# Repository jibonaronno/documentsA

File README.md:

# PDA IEC-61850 References

1. __LU_102_A__ Backup
2. __LU_104_A__ Backup
3. __ClientProc__ executable with SA_Client.ini and YH.cid files Backup
4. __SclManager__ Backup
___
SA_Client.ini has following configs:
```ini
LocalIp=192.168.10.105
...
...
PATH=D:/develop/MZAutomation/SAProgram/ClientProc_2017_Dev_NoTimer_Minsu/ClientProc/61850_CFG/CFG/61850/SA_CFG
SAVE_PATH =D:/develop/MZAutomation/SAProgram/ClientProc_2017_Dev_NoTimer_Minsu/ClientProc/61850_CFG/LOG/61850
ENG_PATH =D:/develop/MZAutomation/SAProgram/ClientProc_2017_Dev_NoTimer_Minsu/ClientProc/61850_CFG/DB/ied_info_gw.csv
```
These configurations should be changed if machine or location is changed. 

It is required to change settings using __SCLManager.exe__ when required for new setup.

<br>

Confluence Pages From PDA
ACQ Operation and calculation / Integration of various current values
Copy of 차단기 동작 특성 페이지
https://jlee193.atlassian.net/wiki/spaces/PDA/pages/514129921/Copy+of

Bushing Documentation Page From PDA 
부싱 누설 전류 페이지
https://jlee193.atlassian.net/wiki/spaces/PDA/pages/296812597

An Initial Concept of hardware pptx file downloaded in Confluence folder
종합예방진단시스템(20210625)_HW팀.pptx
하드웨어 구성
https://jlee193.atlassian.net/wiki/spaces/PDA/pages/154042616

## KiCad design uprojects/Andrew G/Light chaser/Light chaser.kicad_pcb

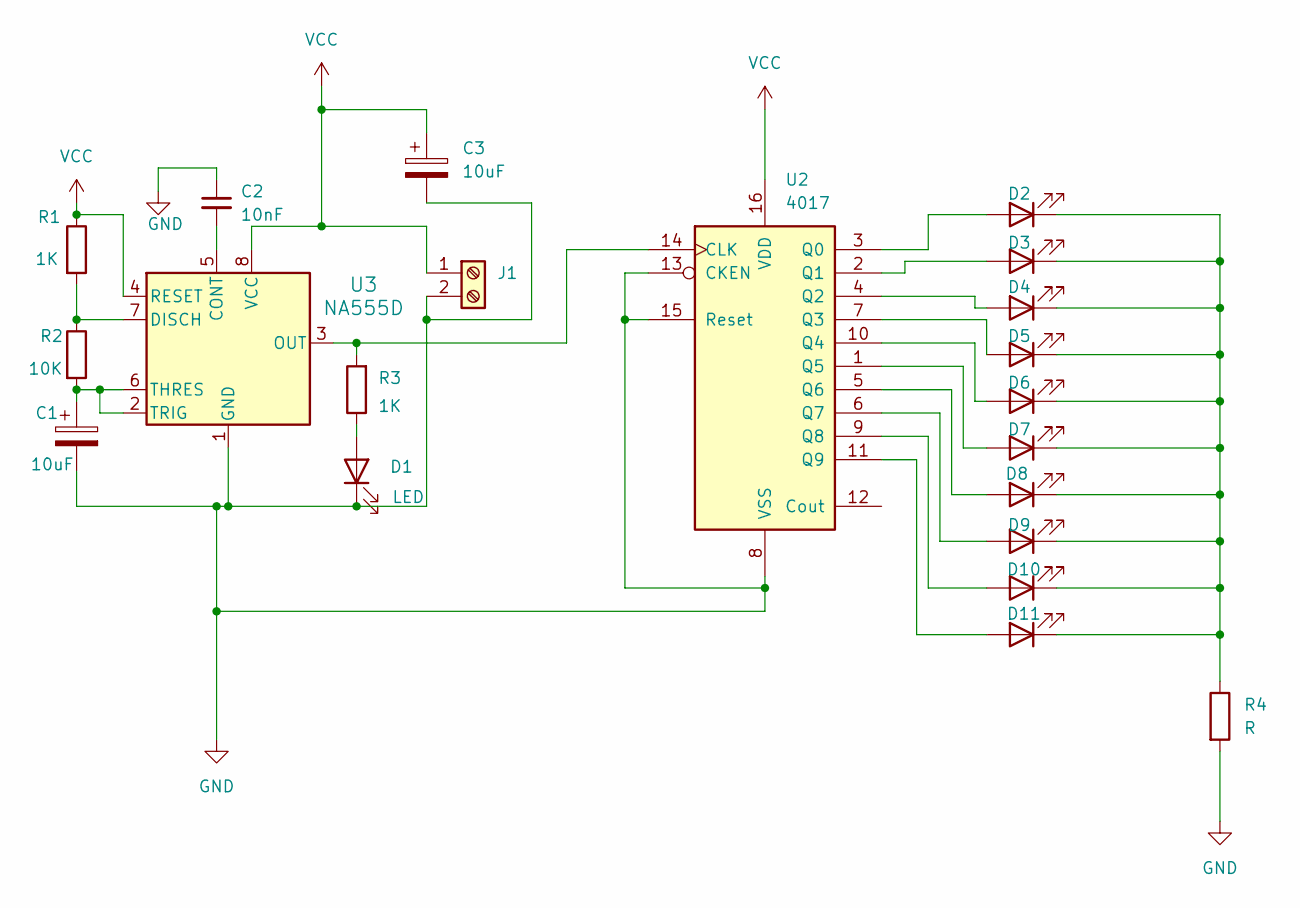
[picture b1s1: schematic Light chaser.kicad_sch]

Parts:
C1: 10uF; CP_Radial_D5.0mm_P2.00mm
C2: 10nF; C_Disc_D3.0mm_W1.6mm_P2.50mm
C3: 10uF; CP_Radial_D10.0mm_P5.00mm
D1, D2, D3, D4, D5, D6, D7, D8, D9, D10, D11: LED; LED_D5.0mm
J1: Screw_Terminal_01x02; TerminalBlock_MaiXu_MX126-5.0-02P_1x02_P5.00mm
R1, R3: 1K; R_Axial_DIN0204_L3.6mm_D1.6mm_P7.62mm_Horizontal
R2: 10K; R_Axial_DIN0204_L3.6mm_D1.6mm_P7.62mm_Horizontal
R4: R; R_Axial_DIN0204_L3.6mm_D1.6mm_P7.62mm_Horizontal
U2: 4017; SO-16_3.9x9.9mm_P1.27mm
U3: NA555D; D8

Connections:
GND: C1.2, C2.1, C3.2, D1.1 (K), J1.2, R4.2, U2.8 (VSS), U2.13 (CKEN), U2.15 (Reset), U3.1 (GND)
unnamed: D1.2 (A), R3.1
unnamed: D2.2 (A), U2.3 (Q0)
unnamed: D3.2 (A), U2.2 (Q1)
unnamed: D4.2 (A), U2.4 (Q2)
unnamed: D5.2 (A), U2.7 (Q3)
unnamed: D6.2 (A), U2.10 (Q4)
unnamed: D7.2 (A), U2.1 (Q5)
unnamed: D8.2 (A), U2.5 (Q6)
unnamed: D9.2 (A), U2.6 (Q7)
unnamed: D10.2 (A), U2.9 (Q8)
unnamed: D2.1 (K), D3.1 (K), D4.1 (K), D5.1 (K), D6.1 (K), D7.1 (K), D8.1 (K), D9.1 (K), D10.1 (K), D11.1 (K), R4.1
unnamed: D11.2 (A), U2.11 (Q9)
unnamed: R3.2, U2.14 (CLK), U3.3 (OUT)
unnamed: C2.2, U3.5 (CONT)
unnamed: R1.2, R2.1, U3.7 (DISCH)
unnamed: C1.1, R2.2, U3.2 (TRIG), U3.6 (THRES)
VCC: C3.1, J1.1, R1.1, U2.16 (VDD), U3.4 (RESET), U3.8 (VCC)

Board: 2 copper layers, 21 parts (0 on the bottom side), 18 nets, no tracks yet.

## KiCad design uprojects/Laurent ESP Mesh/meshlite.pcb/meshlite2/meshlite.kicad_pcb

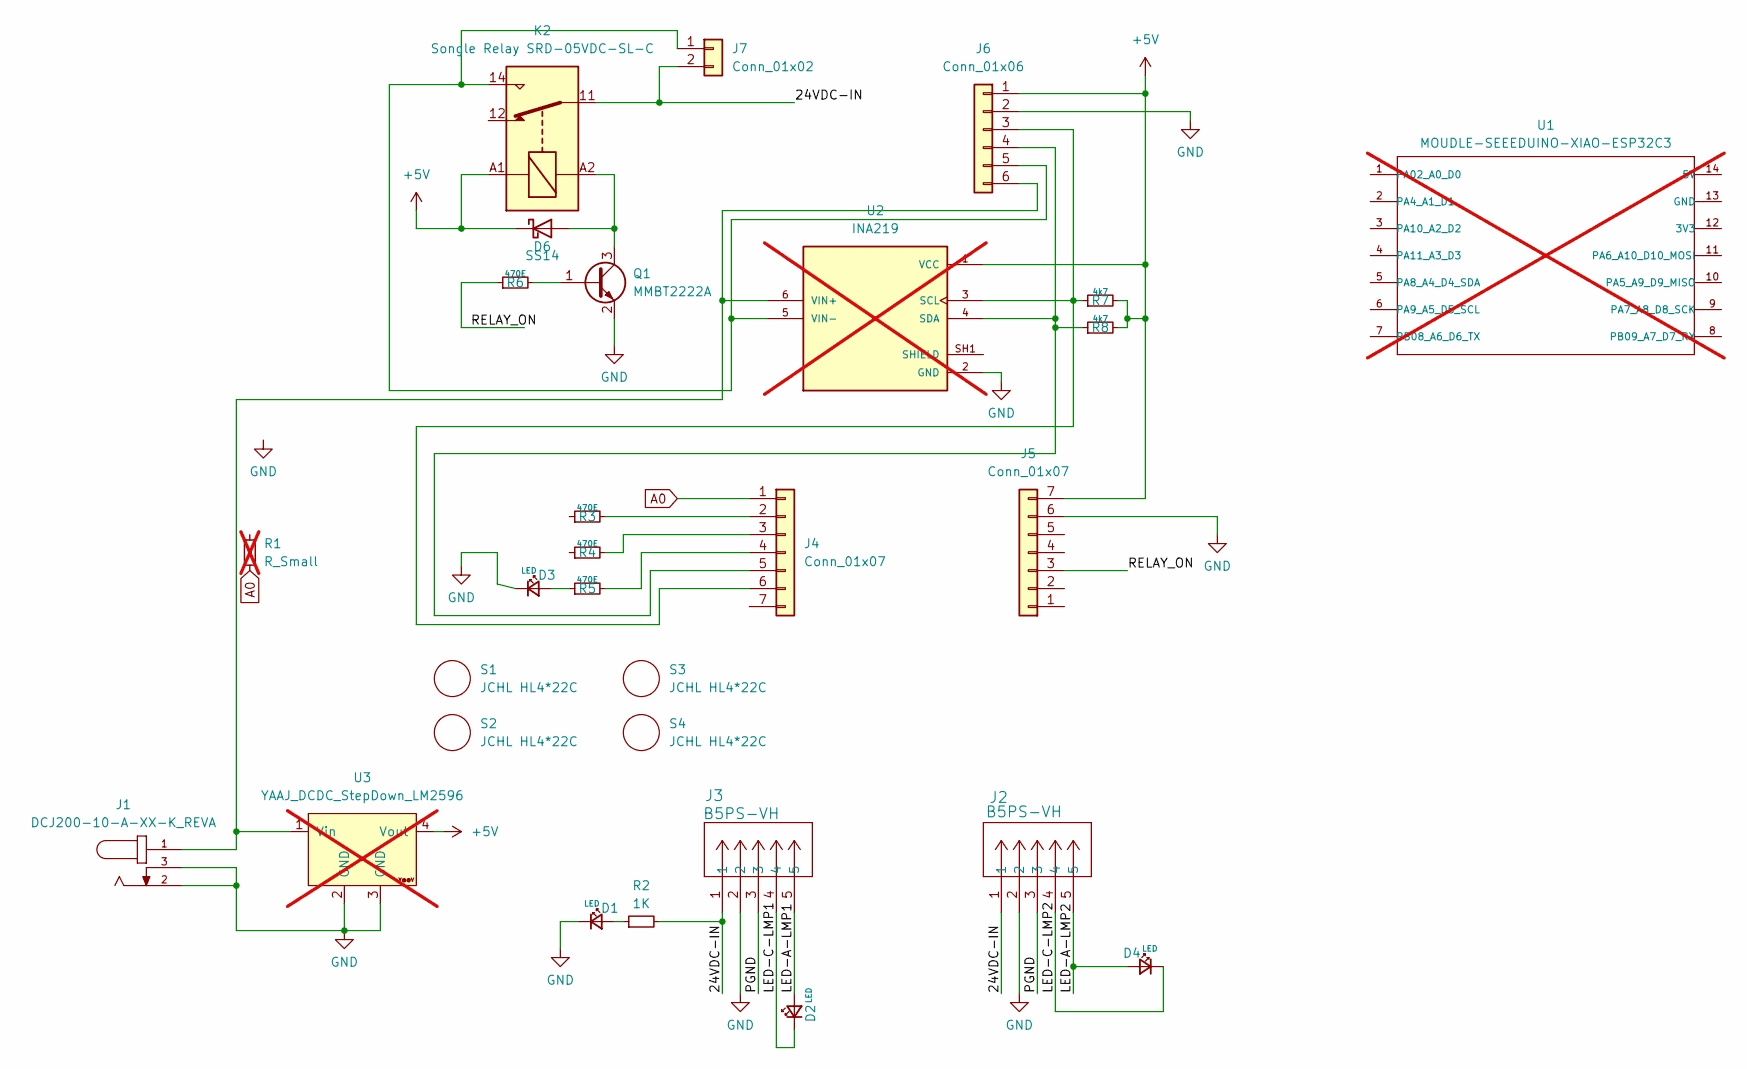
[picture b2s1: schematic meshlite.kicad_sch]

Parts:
D1, D2, D3, D4: LED; LED_D3.0mm; LCSC C473831
D6: SS14; D_SMA; LCSC C83852
J1: DCJ200-10-A-XX-K_REVA; GCT_DCJ200-10-A-XX-K_REVA; PARTREV A; LCSC C720557
J2, J3: B5PS-VH; CONN_B5PS-VH_JST; LCSC C157989
J4, J5: Conn_01x07; PinSocket_1x07_P2.54mm_Vertical; LCSC C492406
J6: Conn_01x06; PinSocket_1x06_P2.54mm_Vertical; LCSC C42431807
J7: Conn_01x02; PinHeader_1x02_P2.54mm_Vertical; LCSC C492401
K2: Songle Relay SRD-05VDC-SL-C; Relay_SPDT_Finder_36.11; LCSC C35449
Q1: MMBT2222A; SOT-23; LCSC C82460
R1: R_Small; R_0603_1608Metric; not fitted
R2: 1K; R_0603_1608Metric; LCSC C22548
R3, R4, R5, R6: 470E; R_0603_1608Metric; LCSC C114669
R7, R8: 4k7; R_0603_1608Metric; LCSC C99782
S1, S2, S3, S4: JCHL HL4*22C; SPACER_01; LCSC C48735534
U1: MOUDLE-SEEEDUINO-XIAO-ESP32C3; MOUDLE14P-SMD-2.54-21X17.8MM; not fitted
U2: INA219; MODULE_INA219; PARTREV C; not fitted
U3: YAAJ_DCDC_StepDown_LM2596; not fitted

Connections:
+5V: D6.1 (K), J5.7, J6.1, K2.A1, R7.2, R8.2, U2.1 (VCC), U3.4 (Vout)
/24VDC-IN: J2.1, J3.1, J7.2, K2.11, R2.2
/LED-A-LMP1: D2.2 (A), J3.5
/LED-A-LMP2: D4.2 (A), J2.5
/LED-C-LMP1: D2.1 (K), J3.4
/LED-C-LMP2: D4.1 (K), J2.4
/PGND: J2.3, J3.3
/RELAY_ON: J4.7, J5.3, R6.1
A0: J4.1, R1.2
GND: D1.1 (K), D3.1 (K), J1.2, J1.3, J2.2, J3.2, J5.6, J6.2, Q1.2 (E), U2.2 (GND), U3.2 (GND), U3.3 (GND)
unnamed: D1.2 (A), R2.1
unnamed: D3.2 (A), R5.1
unnamed: D6.2 (A), K2.A2, Q1.3 (C)
unnamed: J4.2, R3.2
unnamed: J4.3, R4.2
unnamed: J4.4, R5.2
unnamed: J4.5, J6.4, R8.1, U2.4 (SDA)
unnamed: J4.6, J6.3, R7.1, U2.3 (SCL)
unnamed: J6.5, J7.1, K2.14, U2.5 (VIN-), U2.VIN-
unnamed: J1.1, J6.6, U2.6 (VIN+), U2.VIN+, U3.1 (Vin)
unnamed: Q1.1 (B), R6.2
unnamed: U2.SH1 (SHIELD), U2.SH2 (SHIELD), U2.SH3 (SHIELD), U2.SH4 (SHIELD)

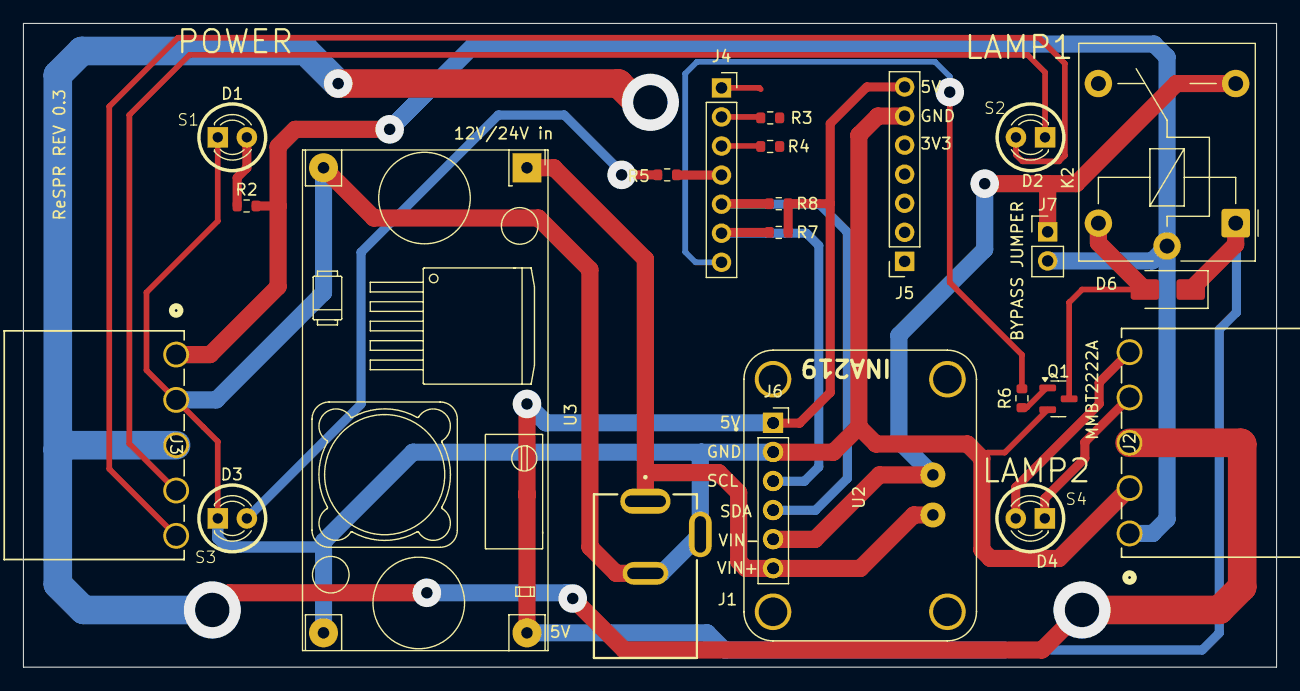
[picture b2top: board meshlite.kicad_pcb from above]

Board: 2 copper layers, 109.5 x 56.2 mm, 27 parts (0 on the bottom side), 21 nets.

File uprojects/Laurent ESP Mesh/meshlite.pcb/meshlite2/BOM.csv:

"Reference","Qty","Value","LCSC"
"D1,D2,D3,D4","4","LED","C473831"
"D6","1","SS14","C83852"
"J1","1","DCJ200-10-A-XX-K_REVA","C720557"
"J2,J3","2","B5PS-VH","C157989"
"J4,J5","2","Conn_01x07","C492406"
"J6","1","Conn_01x06","C42431807"
"J7","1","Conn_01x02","C492401"
"K2","1","Songle Relay SRD-05VDC-SL-C","C35449"
"Q1","1","MMBT2222A","C82460"
"R2","1","1K","C22548"
"R3,R4,R5,R6","4","470E","C114669"
"R7,R8","2","4k7","C99782"
"S1,S2,S3,S4","4","JCHL HL4*22C","C48735534"

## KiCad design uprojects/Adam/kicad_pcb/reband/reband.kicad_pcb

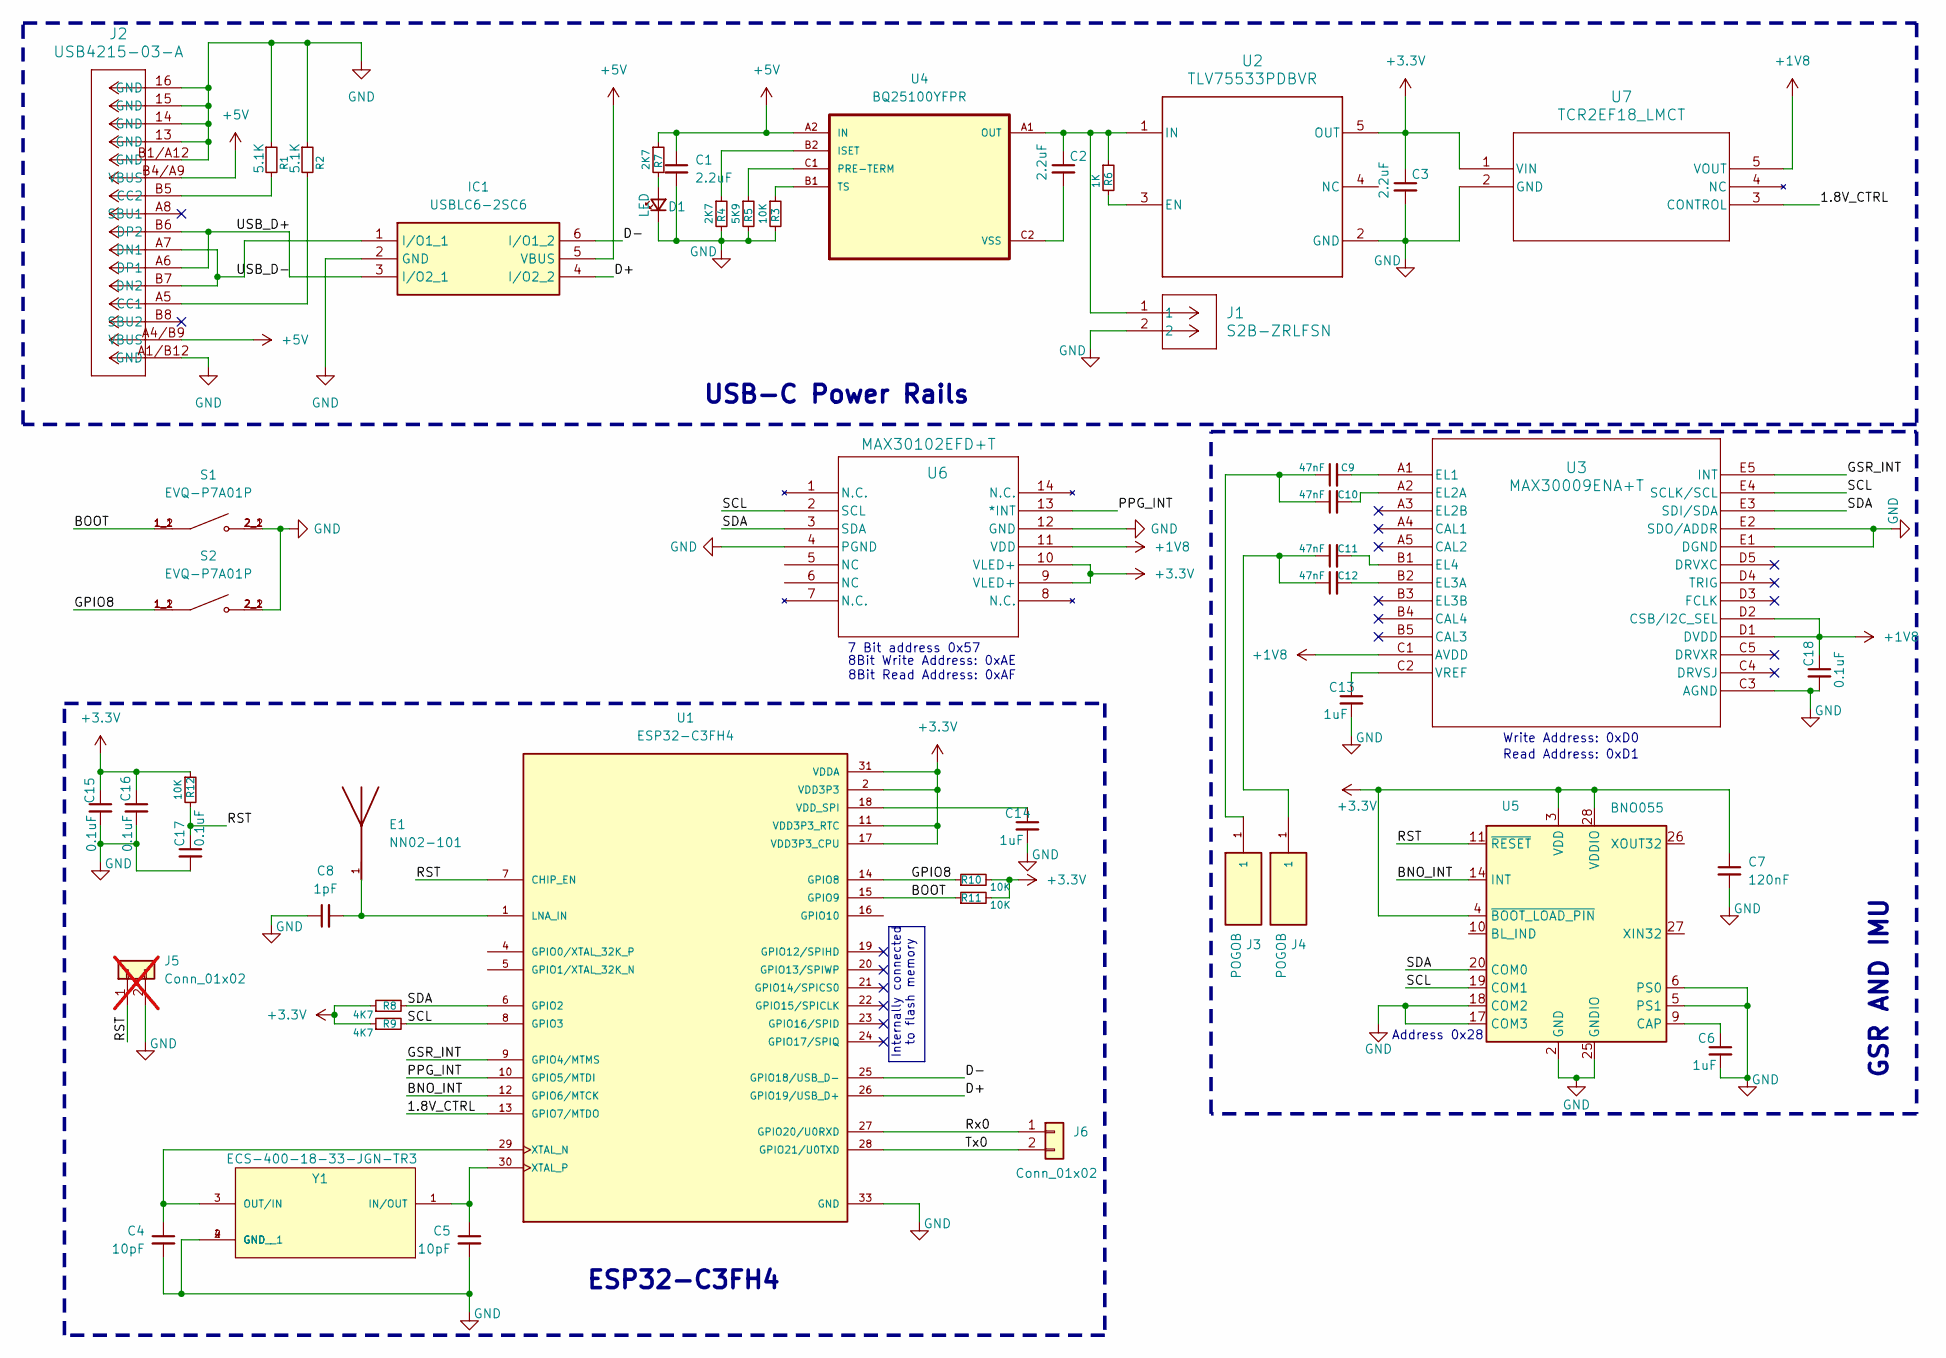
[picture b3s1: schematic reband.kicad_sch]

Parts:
C1, C2, C3: 2.2uF; C_0402_1005Metric_Pad0.74x0.62mm_HandSolder; Manufacturer_Part_Number TMK105CBJ225MV-F; DigiKey 587-6022-2-ND
C4, C5: 10pF; C_0402_1005Metric_Pad0.74x0.62mm_HandSolder; Manufacturer_Part_Number GRM1555C1H100FA01D; DigiKey 490-6186-2-ND
C6, C13, C14: 1uF; C_0402_1005Metric_Pad0.74x0.62mm_HandSolder; Manufacturer_Part_Number JMK105BJ105KV-F; DigiKey 587-1231-2-ND
C7: 120nF; C_0402_1005Metric_Pad0.74x0.62mm_HandSolder; Manufacturer_Part_Number CC0402KRX5R6BB124; DigiKey 13-CC0402KRX5R6BB124TR-ND
C8: 1pF; C_0402_1005Metric_Pad0.74x0.62mm_HandSolder; Manufacturer_Part_Number GJM1555C1H1R0BB01D; DigiKey 490-6073-2-ND
C9, C10, C11, C12: 47nF; C_0402_1005Metric_Pad0.74x0.62mm_HandSolder; Manufacturer_Part_Number GRM155R71H472KA01D; DigiKey 490-1308-2-ND
C15, C16, C17, C18: 0.1uF; C_0402_1005Metric_Pad0.74x0.62mm_HandSolder; Manufacturer_Part_Number CL05B104KP5NNNC; DigiKey 1276-1002-2-ND
D1: LED; LED_0402_1005Metric_Pad0.77x0.64mm_HandSolder; Manufacturer_Part_Number XZMDK68W-2; DigiKey 1497-1174-2-ND
E1: NN02-101; XCVR_NN02-101; PARTREV May 2021; DigiKey 2115-NN02-101TR-ND
IC1: USBLC6-2SC6; SOT95P280X145-6N; Manufacturer_Part_Number USBLC6-2SC6; Mouser Part Number 511-USBLC6-2SC6
J1: S2B-ZRLFSN; CONN_S2B-ZR_JST; Manufacturer_Part_Number S2B-ZR; DigiKey 455-1669-ND
J2: USB4215-03-A; CONN_8p94X6p5X3p16_12L_GCC; Manufacturer_Part_Number USB4215-03-A; DigiKey 2073-USB4215-03-ATR-ND
J3, J4: POGOB; PARTREV N/A; DigiKey ED90453TR-ND
J5: Conn_01x02; PinHeader_1x02_P1.00mm_Vertical; Manufacturer_Part_Number BC020-02-A-0200-0300-L-G; DigiKey 2073-BC020-02-A-0200-0300-L-G-ND; not fitted
J6: Conn_01x02; PinHeader_1x02_P1.00mm_Vertical_SMD_Pin1Left
R1, R2: 5.1K; R_0402_1005Metric_Pad0.72x0.64mm_HandSolder; Manufacturer_Part_Number RC0402FR-075K1L; DigiKey 311-5.10KLRTR-ND
R3, R10, R11, R12: 10K; R_0402_1005Metric_Pad0.72x0.64mm_HandSolder; Manufacturer_Part_Number RMCF0402FT10K0; DigiKey RMCF0402FT10K0TR-ND
R4, R7: 2K7; R_0402_1005Metric_Pad0.72x0.64mm_HandSolder; Manufacturer_Part_Number CRGCQ0402F2K7; DigiKey A129632TR-ND
R5: 5K9; R_0402_1005Metric_Pad0.72x0.64mm_HandSolder; Manufacturer_Part_Number ERJ-2RKF5901X; DigiKey P5.90KLTR-ND
R6: 1K; R_0402_1005Metric_Pad0.72x0.64mm_HandSolder; Manufacturer_Part_Number RC0402FR-071KL; DigiKey 311-1.00KLRTR-ND
R8, R9: 4K7; R_0402_1005Metric_Pad0.72x0.64mm_HandSolder; Manufacturer_Part_Number RC0402JR-074K7L; DigiKey 311-4.7KJRTR-ND
S1, S2: EVQ-P7A01P; SW_EVQ-P7A01P; PARTREV 2022.4; DigiKey P16763TR-ND
U1: ESP32-C3FH4; QFN50P500X500X90-33N; PARTREV 2.0; DigiKey 1904-ESP32-C3FH4TR-ND
U2: TLV75533PDBVR; DBV0005A_N; Manufacturer_Part_Number TLV75533PDBVR; DigiKey 296-50411-2-ND
U3: MAX30009ENA+T; MAX30009ENA_T; Manufacturer_Part_Number MAX30009ENA+T; DigiKey 175-MAX30009ENA+TTR-ND
U4: BQ25100YFPR; BGA6N40P3X2_157X88X50N; Manufacturer_Part_Number BQ25100YFPR; DigiKey 296-39931-2-ND
U5: BNO055; LGA-28_5.2x3.8mm_P0.5mm; Manufacturer_Part_Number BNO055; DigiKey 828-1058-2-ND
U6: MAX30102EFD+T; 21-1048_F143A5&plus_1_MXM; Manufacturer_Part_Number MAX30102EFD+T; DigiKey MAX30102EFD+TTR-ND
U7: TCR2EF18_LMCT; SOT-25 SMV_TOS; Manufacturer_Part_Number TCR2EF18,LM(CT; DigiKey TCR2EF18LM(CTTR-ND
Y1: ECS-400-18-33-JGN-TR3; XTAL_ECS-400-18-33-JGN-TR3; Manufacturer_Part_Number ECS-400-18-33-JGN-TR3; DigiKey 50-ECS-400-18-33-JGN-TR3TR-ND

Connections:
+1V8: C18.1, U3.C1 (AVDD), U3.D1 (DVDD), U3.D2 (CSB/I2C_SEL), U6.11 (VDD), U7.5 (VOUT)
+3.3V: C3.1, C7.1, C15.1, C16.1, R8.1, R9.1, R10.2, R11.2, R12.1, U1.2 (VDD3P3), U1.3 (VDD3P3), U1.11 (VDD3P3_RTC), U1.17 (VDD3P3_CPU), U1.31 (VDDA), U1.32 (VDDA), U2.5 (OUT), U5.3 (VDD), U5.4 (~BOOT_LOAD_PIN), U5.28 (VDDIO), U6.9 (VLED+), U6.10 (VLED+), U7.1 (VIN)
+5V: C1.1, IC1.5 (VBUS), J2.A4/B9 (VBUS), J2.B4/A9 (VBUS), R7.1, U4.A2 (IN)
/1.8V_CTRL: U1.13 (GPIO7/MTDO), U7.3 (CONTROL)
/BNO_INT: U1.12 (GPIO6/MTCK), U5.14 (INT)
/BOOT: R11.1, S1.1_1, S1.1_2, U1.15 (GPIO9)
/D+: IC1.4 (I/O2_2), U1.26 (GPIO19/USB_D+)
/D-: IC1.6 (I/O1_2), U1.25 (GPIO18/USB_D-)
/GPIO8: R10.1, S2.1_1, S2.1_2, U1.14 (GPIO8)
/GSR_INT: U1.9 (GPIO4/MTMS), U3.E5 (INT)
/PPG_INT: U1.10 (GPIO5/MTDI), U6.13 (*INT)
/RST: C17.1, J5.1, R12.2, U1.7 (CHIP_EN), U5.11 (~RESET)
/Rx0: J6.1, U1.27 (GPIO20/U0RXD)
/SCL: R9.2, U1.8 (GPIO3), U3.E4 (SCLK/SCL), U5.19 (COM1), U6.2 (SCL)
/SDA: R8.2, U1.6 (GPIO2), U3.E3 (SDI/SDA), U5.20 (COM0), U6.3 (SDA)
/Tx0: J6.2, U1.28 (GPIO21/U0TXD)
/USB_D+: IC1.3 (I/O2_1), J2.A6 (DP1), J2.B6 (DP2)
/USB_D-: IC1.1 (I/O1_1), J2.A7 (DN1), J2.B7 (DN2)
unnamed: C9.1, C10.1, J3.1 (1_1)
unnamed: C11.1, C12.1, J4.1 (1_1)
unnamed: D1.2 (A), R7.2
unnamed: J2.A5 (CC1), R2.2
unnamed: J2.B5 (CC2), R1.2
unnamed: C14.1, U1.18 (VDD_SPI)
unnamed: C4.1, U1.29 (XTAL_N), Y1.3 (OUT/IN)
unnamed: C5.1, U1.30 (XTAL_P), Y1.1 (IN/OUT)
unnamed: R6.2, U2.3 (EN)
unnamed: C2.1, J1.1, R6.1, U2.1 (IN), U4.A1 (OUT)
unnamed: C9.2, U3.A1 (EL1)
unnamed: C10.2, U3.A2 (EL2A)
unnamed: C12.2, U3.B2 (EL3A)
unnamed: C11.2, U3.B1 (EL4)
unnamed: C13.1, U3.C2 (VREF)
unnamed: R4.1, U4.B2 (ISET)
unnamed: R5.1, U4.C1 (PRE-TERM)
unnamed: R3.1, U4.B1 (TS)
unnamed: C2.2, U4.C2 (VSS)
unnamed: C6.1, U5.9 (CAP)

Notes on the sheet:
ESP32-C3FH4
Internally connected to flash memory
Write Address: 0xD0
GSR AND IMU
USB-C Power Rails
8Bit Write Address: 0xAE
8Bit Read Address: 0xAF
Read Address: 0xD1
Address 0x28
7 Bit address 0x57

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
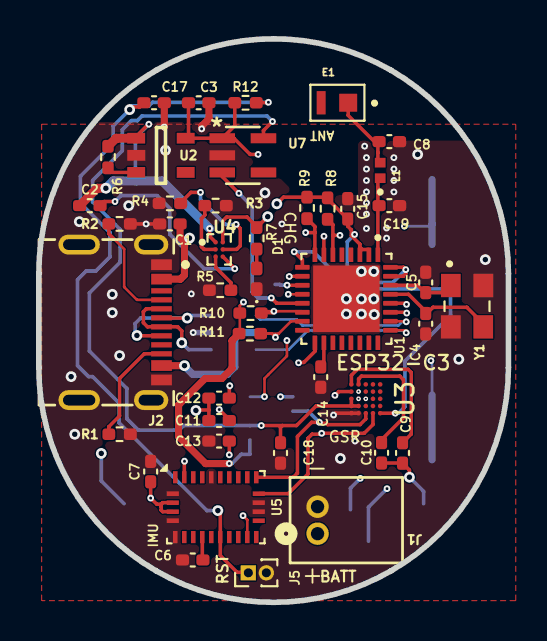
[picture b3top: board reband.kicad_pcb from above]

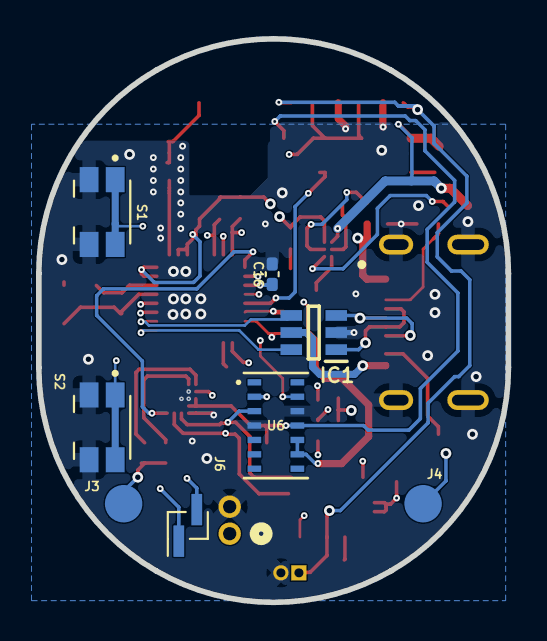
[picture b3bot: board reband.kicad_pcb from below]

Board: 4 copper layers, 26.1 x 31.3 mm, 51 parts (8 on the bottom side), 41 nets.

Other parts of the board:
C19: 3.3pF; C_0402_1005Metric_Pad0.74x0.62mm_HandSolder
L1: LQG15HS2N2B02D; INDC1005X55N

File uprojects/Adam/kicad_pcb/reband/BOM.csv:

"Reference","Qty","Value","Footprint","DigiKey","Manufacturer_Part_Number"
"C1,C2,C3","3","2.2uF","Capacitor_SMD:C_0402_1005Metric_Pad0.74x0.62mm_HandSolder","587-6022-2-ND","TMK105CBJ225MV-F"
"C4,C5","2","27pF","Capacitor_SMD:C_0402_1005Metric_Pad0.74x0.62mm_HandSolder","490-16380-2-ND","GJM1555C1H270FB01D"
"C6,C13,C14","3","1uF","Capacitor_SMD:C_0402_1005Metric_Pad0.74x0.62mm_HandSolder","587-1231-2-ND","JMK105BJ105KV-F"
"C7","1","120nF","Capacitor_SMD:C_0402_1005Metric_Pad0.74x0.62mm_HandSolder","13-CC0402KRX5R6BB124TR-ND","CC0402KRX5R6BB124"
"C8,C19","2","3.3pF","Capacitor_SMD:C_0402_1005Metric_Pad0.74x0.62mm_HandSolder","490-8097-2-ND","GJM1555C1H3R3BB01D"
"C9,C10,C11,C12","4","47nF","Capacitor_SMD:C_0402_1005Metric_Pad0.74x0.62mm_HandSolder","490-1308-2-ND","GRM155R71H472KA01D"
"C15,C16,C17,C18","4","0.1uF","Capacitor_SMD:C_0402_1005Metric_Pad0.74x0.62mm_HandSolder","1276-1002-2-ND","CL05B104KP5NNNC"
"D1","1","LED","LED_SMD:LED_0402_1005Metric_Pad0.77x0.64mm_HandSolder","1497-1174-2-ND","XZMDK68W-2"
"E1","1","NN02-101","NN02_101:XCVR_NN02-101","2115-NN02-101TR-ND","NN02-101"
"IC1","1","USBLC6-2SC6","USBLC6-2SC6:SOT95P280X145-6N","5399-USBLC6-2SC6TR-ND","USBLC6-2SC6"
"J1","1","S2B-ZRLFSN","S2B_ZR_LF_SN:CONN_S2B-ZR_JST","455-1669-ND","S2B-ZR"
"J2","1","USB4215-03-A","USB4215_03_A:CONN_8p94X6p5X3p16_12L_GCC","2073-USB4215-03-ATR-ND","USB4215-03-A"
"J3,J4","2","POGOB","POGO_PINB:POGOB","ED90453TR-ND","0910-0-57-20-76-14-11-0"
"L1","1","LQG15HS2N2B02D","LQG15HS2N2B02D:INDC1005X55N","490-LQG15HS2N2B02DTR-ND","LQG15HS2N2B02D"
"R1,R2","2","5.1K","Resistor_SMD:R_0402_1005Metric_Pad0.72x0.64mm_HandSolder","311-5.10KLRTR-ND","RC0402FR-075K1L"
"R3,R10,R11,R12","4","10K","Resistor_SMD:R_0402_1005Metric_Pad0.72x0.64mm_HandSolder","RMCF0402FT10K0TR-ND","RMCF0402FT10K0"
"R4,R7","2","2K7","Resistor_SMD:R_0402_1005Metric_Pad0.72x0.64mm_HandSolder","A129632TR-ND","CRGCQ0402F2K7"
"R5","1","5K9","Resistor_SMD:R_0402_1005Metric_Pad0.72x0.64mm_HandSolder","P5.90KLTR-ND","ERJ-2RKF5901X"
"R6","1","1K","Resistor_SMD:R_0402_1005Metric_Pad0.72x0.64mm_HandSolder","311-1.00KLRTR-ND","RC0402FR-071KL"
"R8,R9","2","4K7","Resistor_SMD:R_0402_1005Metric_Pad0.72x0.64mm_HandSolder","311-4.7KJRTR-ND","RC0402JR-074K7L"
"S1,S2","2","EVQ-P7A01P","EVQ_P7A01P:SW_EVQ-P7A01P","P16763TR-ND","EVQ-P7A01P"
"U1","1","ESP32-C3FH4","ESP32-C3FH4:QFN50P500X500X90-33N","1904-ESP32-C3FH4TR-ND","ESP32-C3FH4"
"U2","1","TLV75533PDBVR","TLV75533PDBVR:DBV0005A_N","296-50411-2-ND","TLV75533PDBVR"
"U3","1","MAX30009ENA+T","MAX30009ENA_T:MAX30009ENA_T","175-MAX30009ENA+TTR-ND","MAX30009ENA+T"
"U4","1","BQ25100YFPR","BQ25100YFPR:BGA6N40P3X2_157X88X50N","296-39931-2-ND","BQ25100YFPR"
"U5","1","BNO055","Package_LGA:LGA-28_5.2x3.8mm_P0.5mm","828-1058-2-ND","BNO055"
"U6","1","MAX30102EFD+T","MAX30102EFD_T:21-1048_F143A5&plus_1_MXM","MAX30102EFD+TTR-ND","MAX30102EFD+T"
"U7","1","TCR2EF18_LMCT","TCR2EF18_LM_CT:SOT-25   SMV_TOS","TCR2EF18LM(CTTR-ND","TCR2EF18,LM(CT"
"Y1","1","ECS-400-18-33-JGN-TR3","ECS_400_18_33_JGN_TR3:XTAL_ECS-400-18-33-JGN-TR3","50-ECS-400-18-33-JGN-TR3TR-ND","ECS-400-18-33-JGN-TR3"

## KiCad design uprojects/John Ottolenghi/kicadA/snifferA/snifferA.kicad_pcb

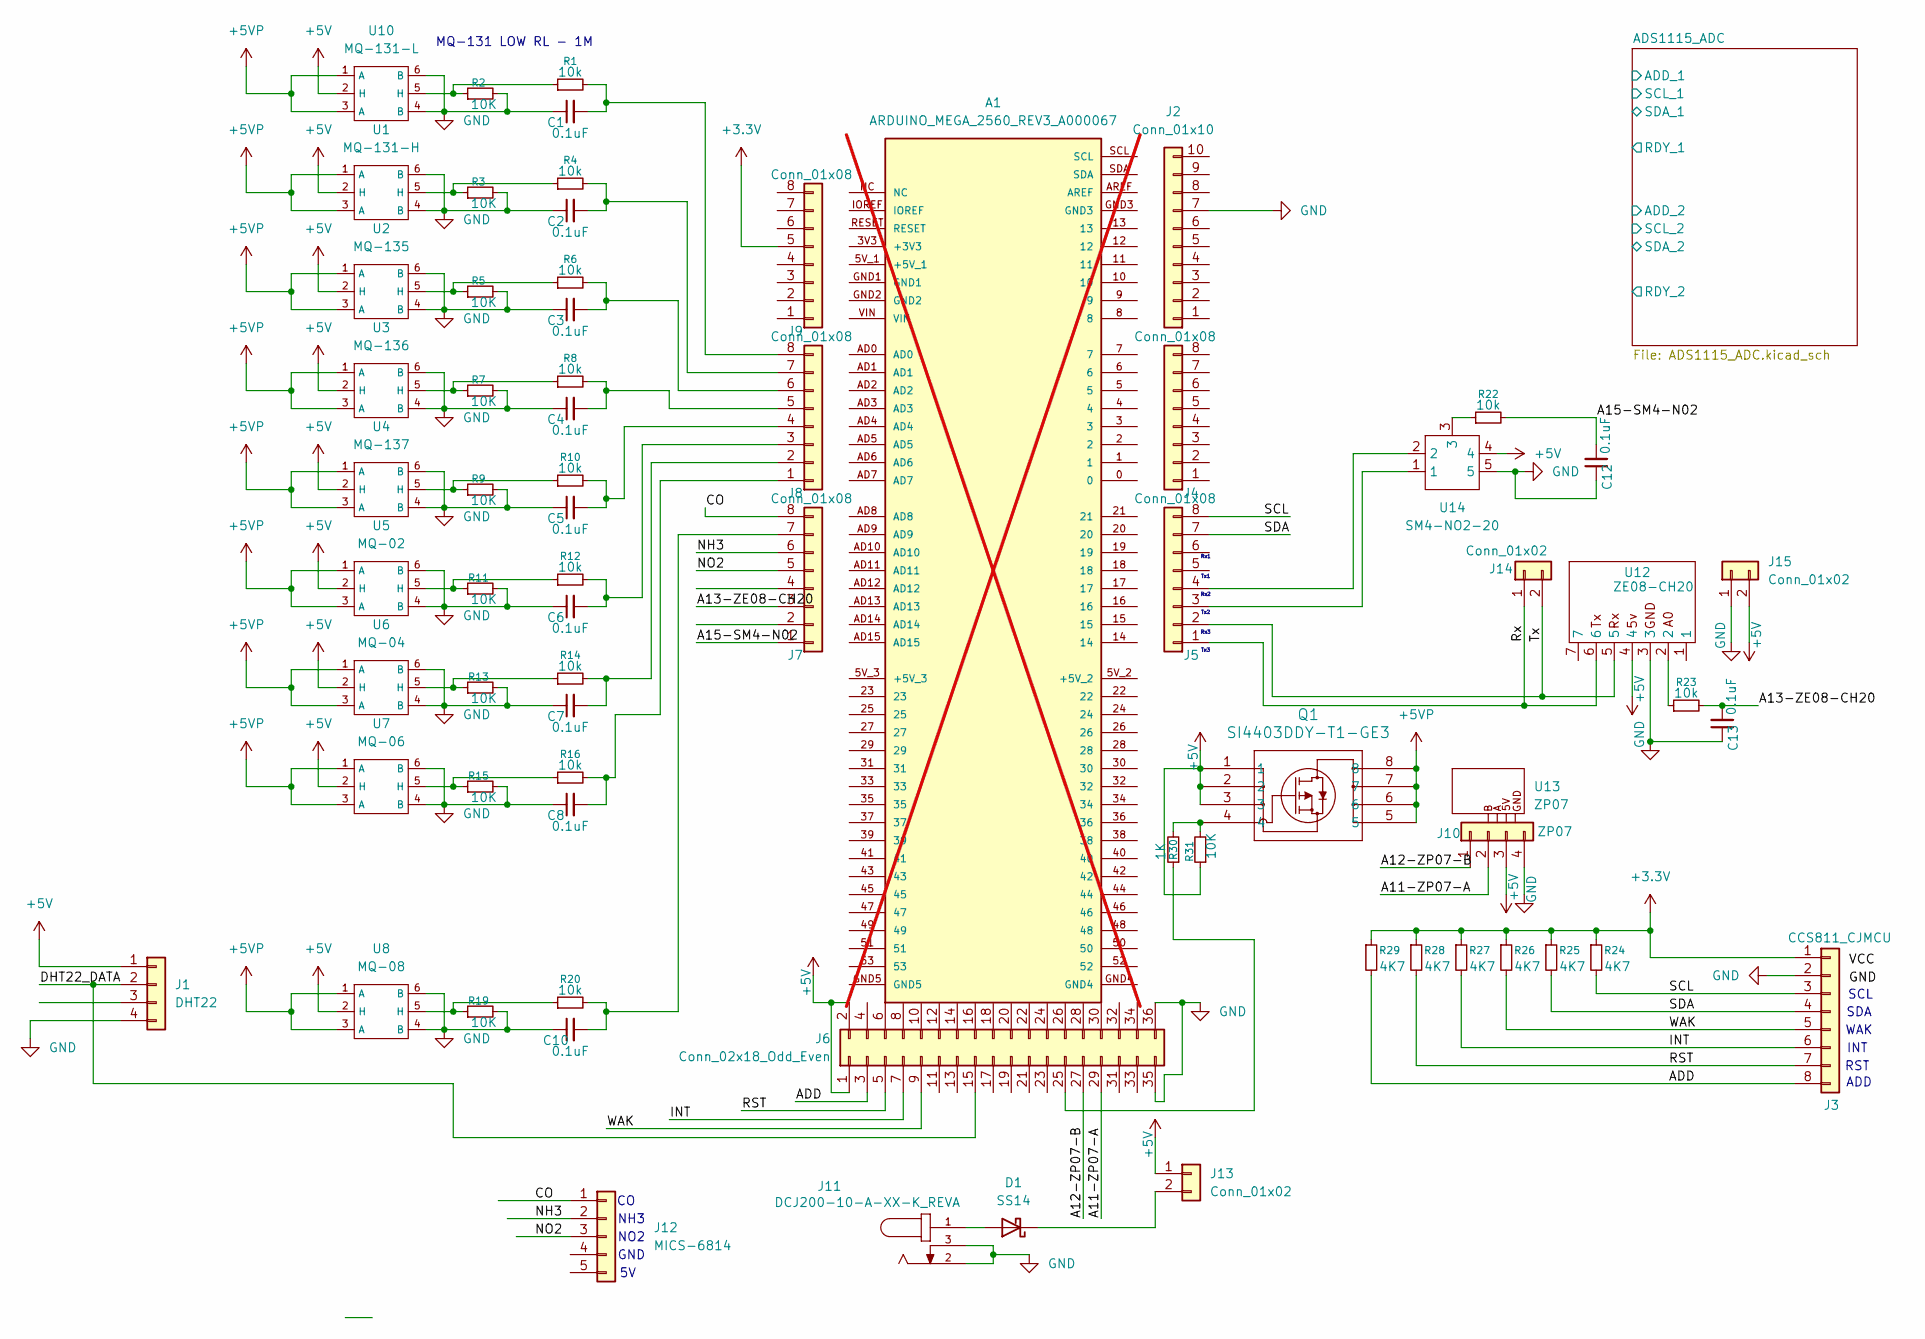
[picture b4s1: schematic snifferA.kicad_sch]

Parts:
A1: ARDUINO_MEGA_2560_REV3_A000067; ARDUINO_ARDUINO_MEGA_2560_REV3_A000067; PARTREV 3; not fitted
C1, C2, C3, C4, C5, C6, C7, C8, C10, C12, C13: 0.1uF; C_1206_3216Metric_Pad1.33x1.80mm_HandSolder; LCSC C24497
D1: SS14; D_SMA
J1: DHT22; PinSocket_1x04_P2.54mm_Vertical
J2: Conn_01x10; PinHeader_1x10_P2.54mm_Vertical; LCSC C42431810
J3: CCS811_CJMCU; PinHeader_1x08_P2.54mm_Vertical; LCSC C6332201
J4, J5, J7, J8, J9: Conn_01x08; PinHeader_1x08_P2.54mm_Vertical; LCSC C6332201
J6: Conn_02x18_Odd_Even; PinHeader_2x18_P2.54mm_Vertical; LCSC C41376109
J10: ZP07; PinSocket_1x04_P2.54mm_Vertical
J11: DCJ200-10-A-XX-K_REVA; GCT_DCJ200-10-A-XX-K_REVA; PARTREV A
J12: MICS-6814; PinSocket_1x05_P2.54mm_Vertical
J13, J14, J15: Conn_01x02; PinHeader_1x02_P2.54mm_Vertical
Q1: SI4403DDY-T1-GE3; SO-8_MS-012_VIS
R1, R4, R6, R8, R10, R12, R14, R16, R20, R22, R23: 10k; R_1206_3216Metric; LCSC C2907370
R2, R3, R5, R7, R9, R11, R13, R15, R19, R31: 10K; R_1206_3216Metric; LCSC C2907370
R24, R25, R26, R27, R28, R29: 4K7; R_0603_1608Metric; LCSC C99782
R30: 1K; R_0603_1608Metric_Pad0.98x0.95mm_HandSolder; LCSC C22548
U1: MQ-131-H; MQ
U2: MQ-135; MQ
U3: MQ-136; MQ
U4: MQ-137; MQ
U5: MQ-02; MQ
U6: MQ-04; MQ
U7: MQ-06; MQ
U8: MQ-08; MQ
U10: MQ-131-L; MQ
U12: ZE08-CH20; ZE-08
U13: ZP07; ZP07-FRAME
U14: SM4-NO2-20

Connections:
+3.3V: J3.1, J9.5, R24.1, R25.1, R26.1, R27.1, R28.1, R29.1
+5V: J1.1, J6.1, J6.2, J10.3, J13.1, J15.2, Q1.1, Q1.2, Q1.3, R31.1, U1.2 (H), U2.2 (H), U3.2 (H), U4.2 (H), U5.2 (H), U6.2 (H), U7.2 (H), U8.2 (H), U10.2 (H), U12.4, U14.4
+5VP: Q1.5, Q1.6, Q1.7, Q1.8, U1.1 (A), U1.3 (A), U2.1 (A), U2.3 (A), U3.1 (A), U3.3 (A), U4.1 (A), U4.3 (A), U5.1 (A), U5.3 (A), U6.1 (A), U6.3 (A), U7.1 (A), U7.3 (A), U8.1 (A), U8.3 (A), U10.1 (A), U10.3 (A)
/A11-ZP07-A: J6.29, J10.2
/A12-ZP07-B: J6.27, J10.1
/A13-ZE08-CH20: C13.2, J7.3, R23.2
/A15-SM4-N02: C12.2, J7.1, R22.2
/ADD: J3.8, J6.3, R29.2
/CO: J7.8, J12.1
/DHT22_DATA: J1.2, J6.15
/INT: J3.6, J6.7, R27.2
/NH3: J7.6, J12.2
/NO2: J7.5, J12.3
/RST: J3.7, J6.5, R28.2
/Rx: J5.1, J14.1, U12.6
/SCL: J3.3, J5.8, R24.2
/SDA: J3.4, J5.7, R25.2
/Tx: J5.2, J14.2, U12.5
/WAK: J3.5, J6.9, R26.2
GND: C1.1, C2.1, C3.1, C4.1, C5.1, C6.1, C7.1, C8.1, C10.1, C12.1, C13.1, J1.4, J2.7, J3.2, J6.35, J6.36, J10.4, J11.2, J11.3, J15.1, R2.2, R3.2, R5.2, R7.2, R9.2, R11.2, R13.2, R15.2, R19.2, U1.4 (B), U1.6 (B), U2.4 (B), U2.6 (B), U3.4 (B), U3.6 (B), U4.4 (B), U4.6 (B), U5.4 (B), U5.6 (B), U6.4 (B), U6.6 (B), U7.4 (B), U7.6 (B), U8.4 (B), U8.6 (B), U10.4 (B), U10.6 (B), U12.3, U14.5
unnamed: D1.2 (A), J11.1
unnamed: D1.1 (K), J13.2
unnamed: J5.3, U14.1
unnamed: J5.4, U14.2
unnamed: J6.25, R30.1
unnamed: C10.2, J7.7, R20.2
unnamed: C8.2, J8.1, R16.2
unnamed: C7.2, J8.2, R14.2
unnamed: C6.2, J8.3, R12.2
unnamed: C5.2, J8.4, R10.2
unnamed: C4.2, J8.5, R8.2
unnamed: C3.2, J8.6, R6.2
unnamed: C2.2, J8.7, R4.2
unnamed: C1.2, J8.8, R1.2
unnamed: Q1.4, R30.2, R31.2
unnamed: R1.1, R2.1, U10.5 (H)
unnamed: R3.1, R4.1, U1.5 (H)
unnamed: R5.1, R6.1, U2.5 (H)
unnamed: R7.1, R8.1, U3.5 (H)
unnamed: R9.1, R10.1, U4.5 (H)
unnamed: R11.1, R12.1, U5.5 (H)
unnamed: R13.1, R14.1, U6.5 (H)
unnamed: R15.1, R16.1, U7.5 (H)
unnamed: R19.1, R20.1, U8.5 (H)
unnamed: R22.1, U14.3
unnamed: R23.1, U12.2

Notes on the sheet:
Tx2
NH3
SCL
Tx1
Rx1
SDA
RST
Tx3
NO2
Rx3
WAK
Rx2
INT
MQ-131 LOW RL - 1M
GND
ADD

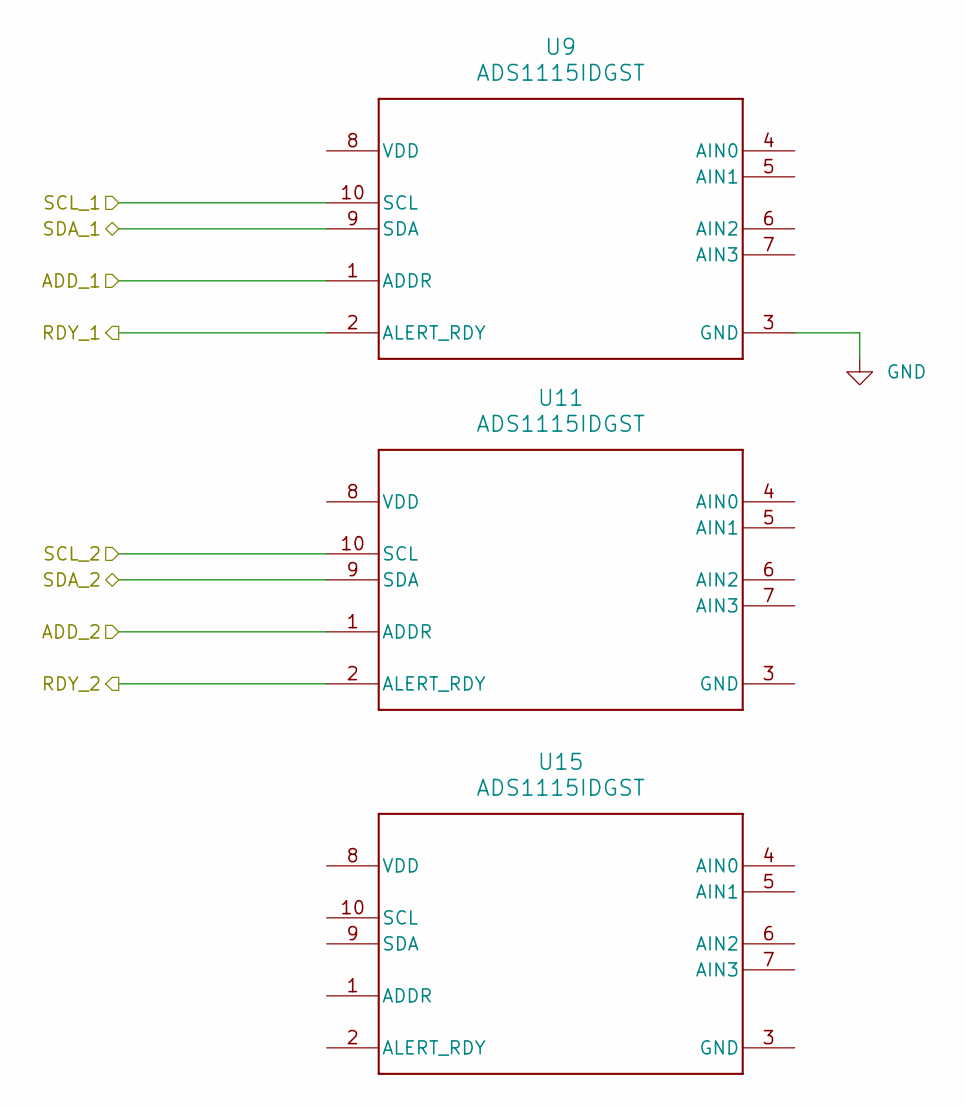
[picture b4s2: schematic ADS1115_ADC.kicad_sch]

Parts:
U9, U11, U15: ADS1115IDGST; DGS0010A_N

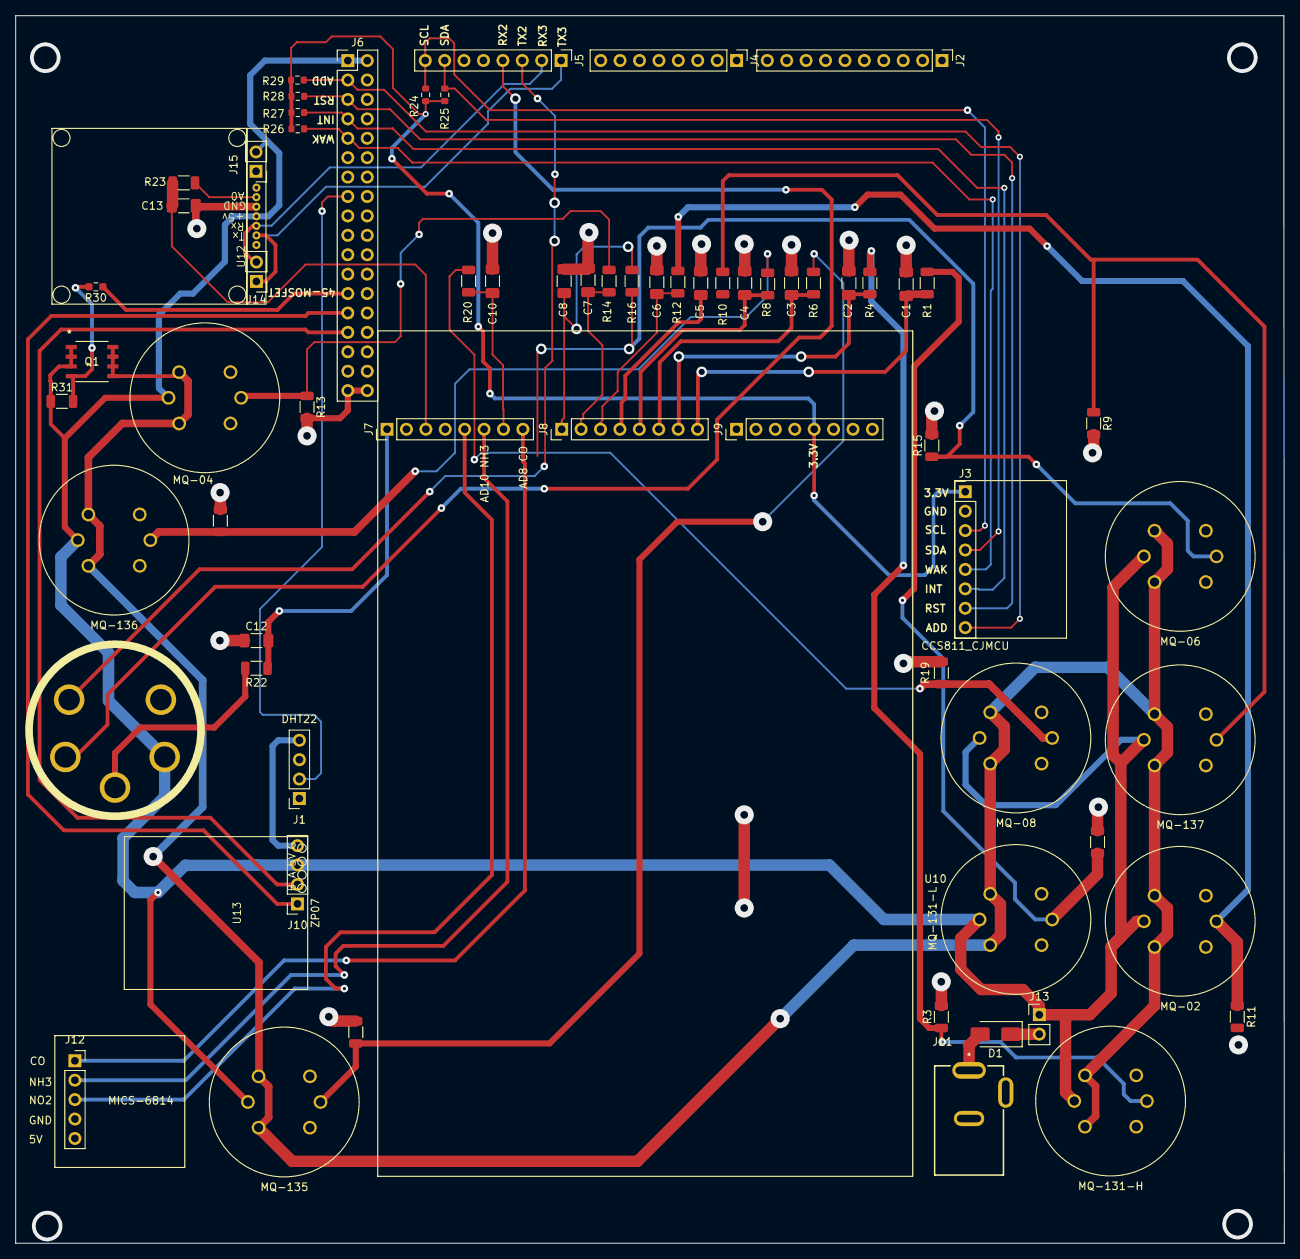
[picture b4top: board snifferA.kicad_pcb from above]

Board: 2 copper layers, 166.0 x 160.6 mm, 68 parts (0 on the bottom side), 46 nets.

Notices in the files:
CM0/CM0_Dev_Board_EDATEK/CM0IO.kicad_sch:
© 2025 Raspberry Pi Ltd
